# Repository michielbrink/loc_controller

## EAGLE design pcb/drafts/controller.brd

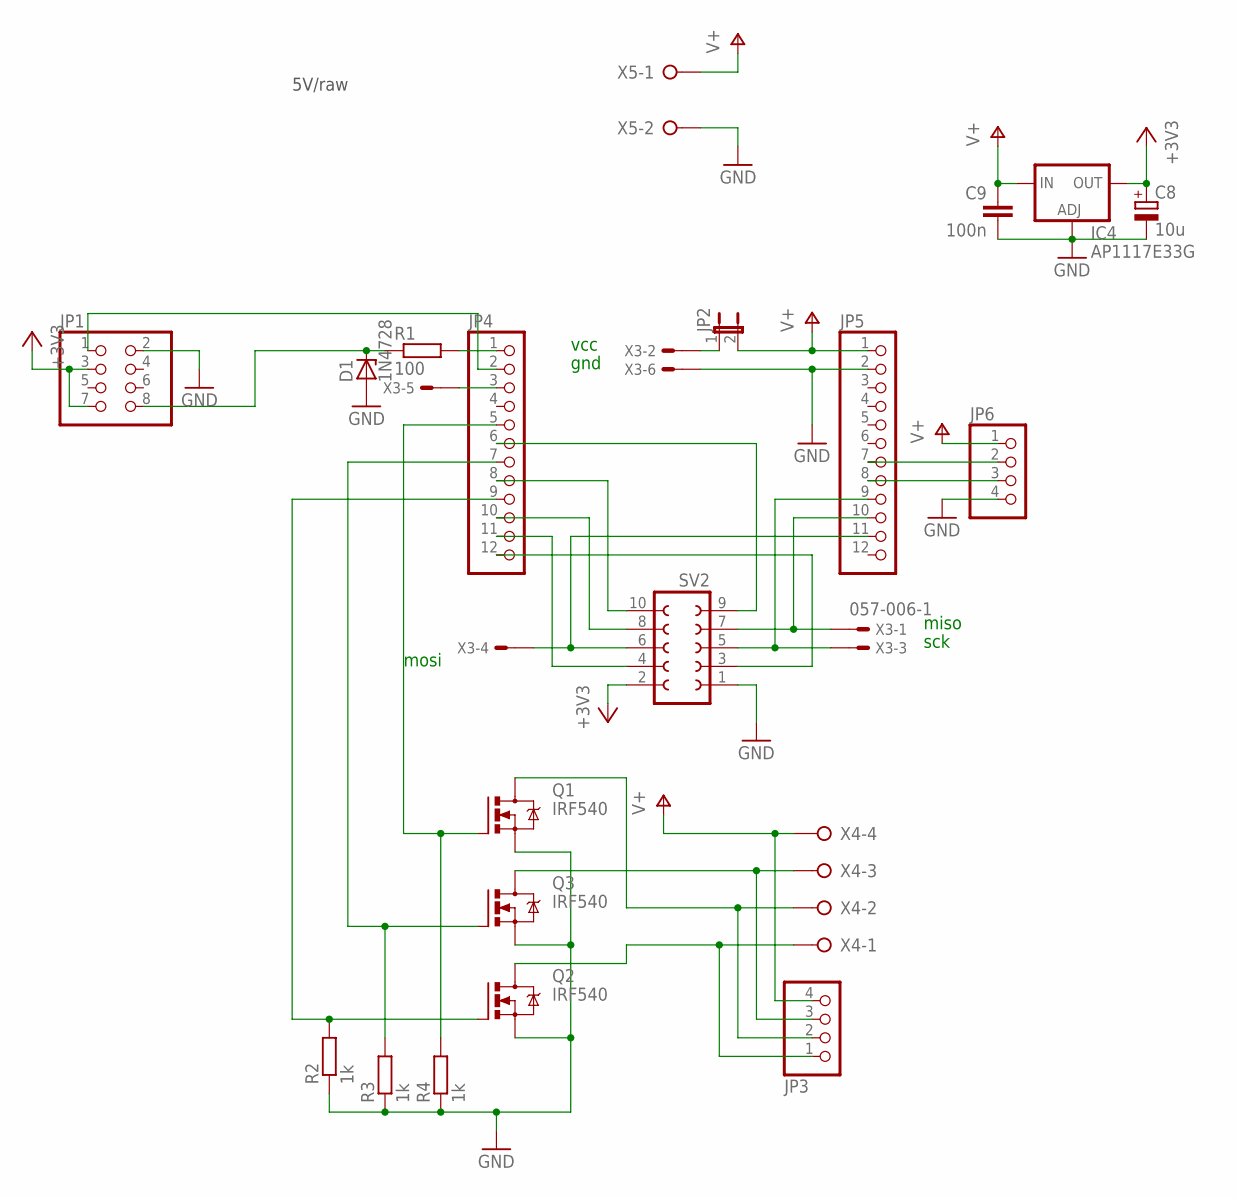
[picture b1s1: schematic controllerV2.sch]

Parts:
C8: 10u; TT2D4L
C9: 100n; C025-025X050
D1: 1N4728; DO41Z10
IC4: AP1117E33G; SOT223
JP1: PINHD-2X4; 2X04
JP2: JP1E; JP1
JP3, JP6: PINHD-1X4; 1X04
JP4, JP5: PINHD-1X12; 1X12
Q1, Q2, Q3: IRF540; TO220BV
R1: 100; 0207/10
R2, R3, R4: 1k; M0805
SV2: FE05-2
X3: 057-006-1
X4: W237-04P; W237-4P
X5: W237-02P; W237-132

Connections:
+3V3: C8.+, IC4.2 (OUT), IC4.4 (OUT), JP1.3, JP1.7, SV2.2
GND: C8.-, C9.2, D1.A, IC4.1 (ADJ), JP1.2, JP5.2, JP6.4, Q1.S, Q2.S, Q3.S, R2.1, R3.1, R4.1, SV2.1, X3.6, X5.2
unnamed: JP4.1, R1.2
unnamed: JP4.3, X3.5
unnamed: JP5.9, SV2.5, X3.3
unnamed: JP5.10, SV2.7, X3.1
unnamed: D1.C, JP1.8, R1.1
unnamed: JP4.9, Q2.G, R2.2
unnamed: JP1.1, JP4.2
unnamed: JP3.1, Q2.D, X4.1
unnamed: JP3.2, Q3.D, X4.2
unnamed: JP3.3, Q1.D, X4.3
unnamed: JP5.11, SV2.6, X3.4
unnamed: JP4.5, Q1.G, R4.2
unnamed: JP4.7, Q3.G, R3.2
unnamed: JP4.12, SV2.3
unnamed: JP4.6, SV2.9
unnamed: JP4.11, SV2.4
unnamed: JP4.10, SV2.8
unnamed: JP4.8, SV2.10
unnamed: JP2.1, X3.2
unnamed: JP5.7, JP6.2
unnamed: JP5.8, JP6.3
V+: C9.1, IC4.3 (IN), JP2.2, JP3.4, JP5.1, JP6.1, X4.4, X5.1

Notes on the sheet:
5V/raw
miso
sck
vcc
gnd
mosi

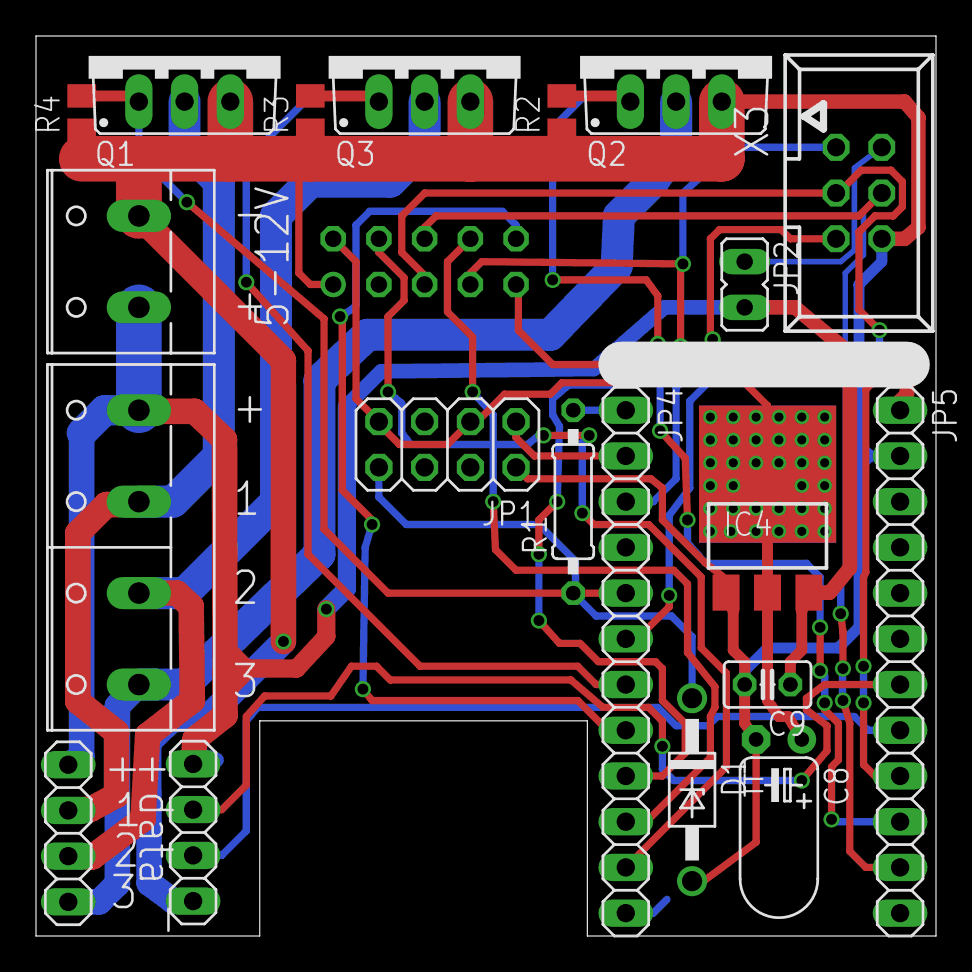
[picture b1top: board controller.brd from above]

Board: 2 copper layers, 50.0 x 50.0 mm, 21 parts (1 on the bottom side), 24 nets.

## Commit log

2015-05-05 change stuff
2015-05-05 add loc
